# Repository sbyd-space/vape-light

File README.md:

# vape flashlight
An educational DIY kit for converting a disposable vape into a rechargeable flashlight

*early prototype of the kit photographed by Daniel Wilkens, used under CC BY 4.0 / cropped from original*

The kit is used in workshops to educate about:
* environmental and social impact of resource extraction
* resource consumption of electronics and disposable products
* basic hands-on soldering skills

It is accompanied by a [zine][zine] containing contextual information about these topics and instructions for assembly.

*rendering of the pcb by Steffen Hartwig, licensed under CC BY 4.0*

The pcbs were developed with [KiCad 8.0][kicad].  
[KiKit 1.6.0][kikit] was used for the panelization of the PCBs for production.  
Visualizations were made with [Blender 4.2][blender] and [pcb2blender 2.15][pcb2blender].  
The fabrication files were generated with [Fabrication Toolkit 5.0.1][fabricationtoolkit].  
The files for 3D printing were generated from [OpenSCAD 2021.01][openscad].  

PCB and 3D printing source files are licensed under **CERN OHL P 2.0**  
Images and visualizations are licensed under **CC BY 4.0** 

The kit, workshop and zine were developed in the project ["Sustainability by Design"][sbyd] as part of the “Innovative University” funding line and is supported by the German Federal Ministry of Research, Technology and Space (BMFTR) and the Joint Science Conference (GWK).

[zine]: https://sbyd.space/wp-content/uploads/2024/09/SBYD-Zine_3_WEB.pdf
[sbyd]: https://sbyd.space/en/

[kicad]: https://www.kicad.org
[kikit]: https://github.com/yaqwsx/KiKit
[blender]: https://www.blender.org
[pcb2blender]: https://github.com/30350n/pcb2blender
[fabricationtoolkit]: https://github.com/bennymeg/JLC-Plugin-for-KiCad
[openscad]: https://openscad.org

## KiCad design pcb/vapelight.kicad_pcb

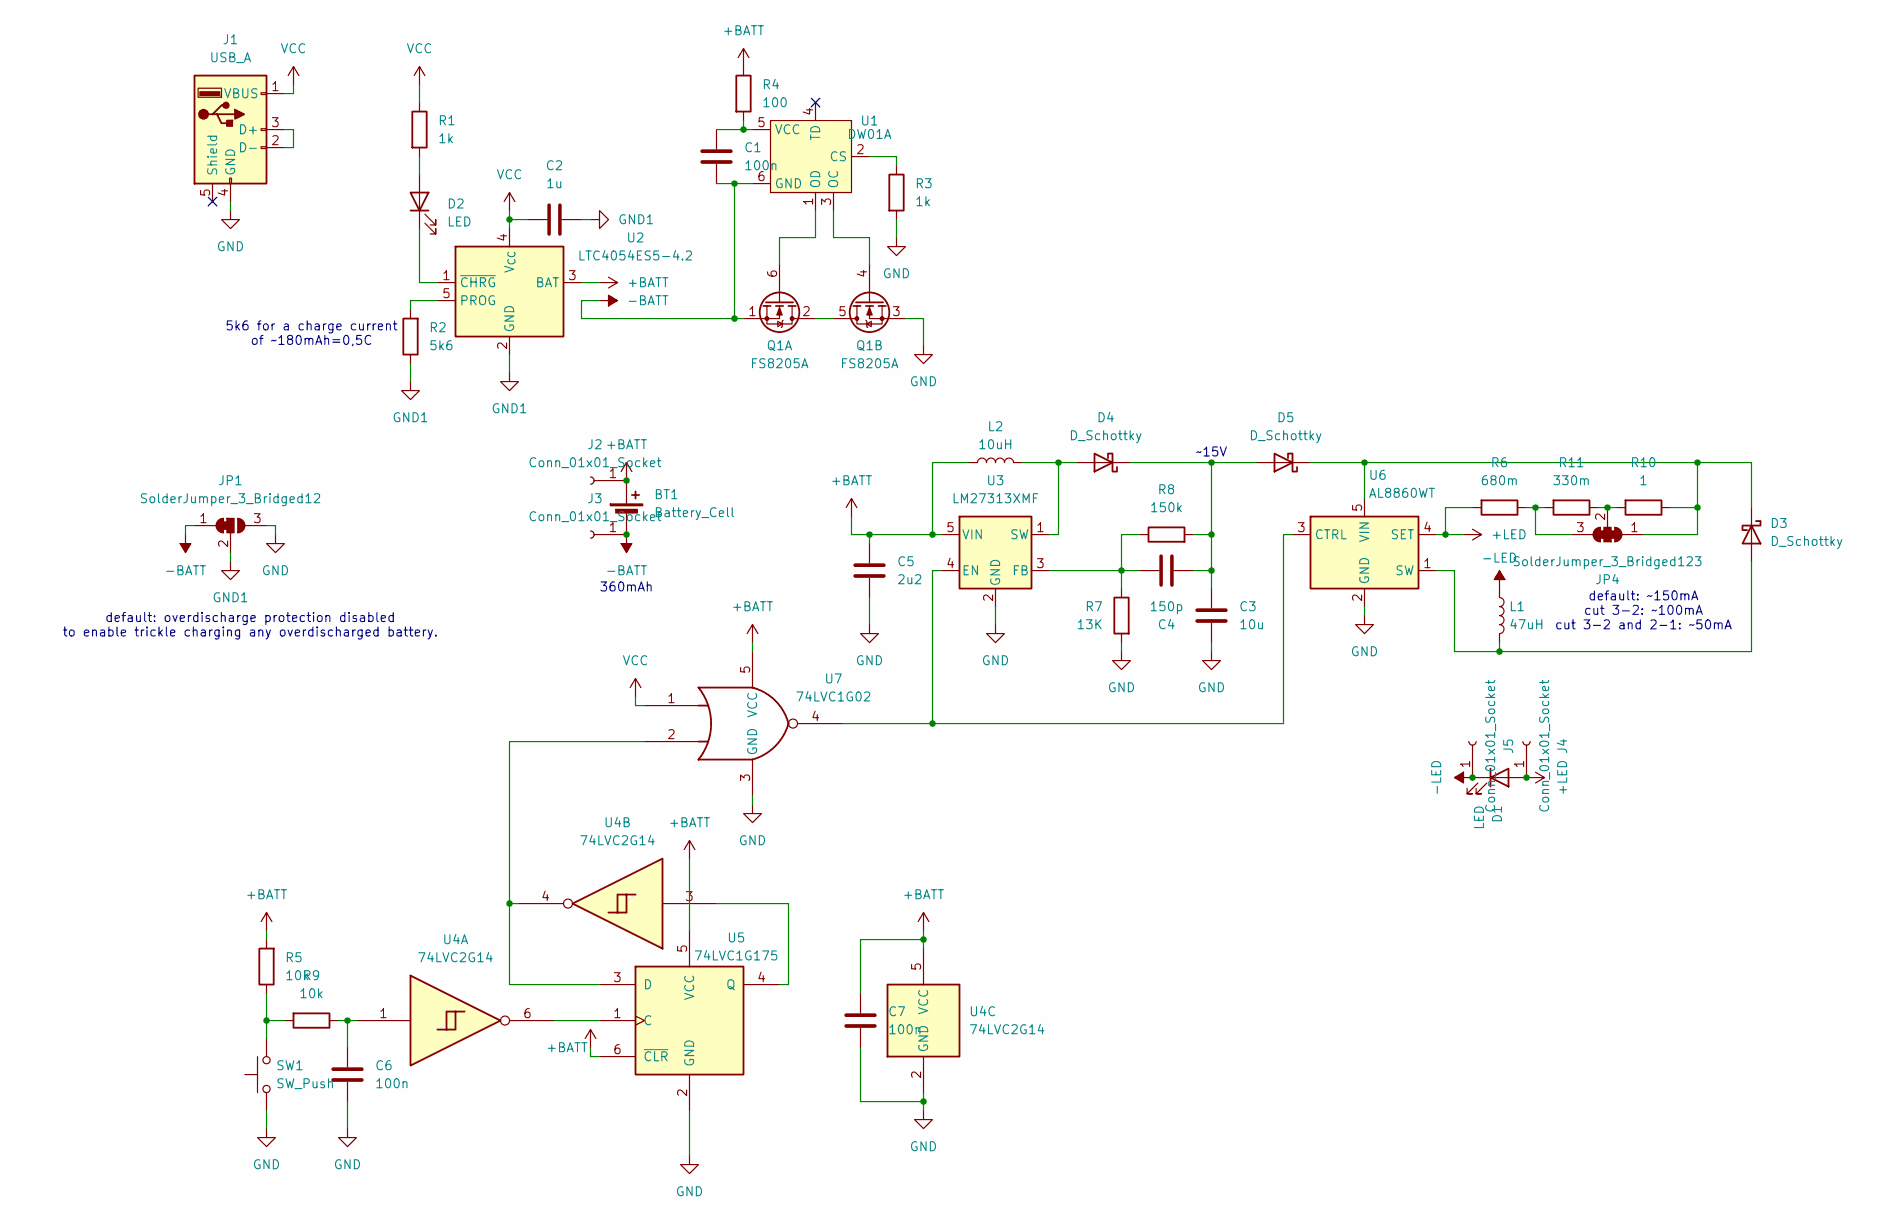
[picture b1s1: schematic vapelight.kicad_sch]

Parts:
BT1: Battery_Cell
C1, C6, C7: 100n; C_0603_1608Metric; LCSC C14663
C2: 1u; C_0603_1608Metric; LCSC C15849
C3: 10u; C_0603_1608Metric; LCSC C96446
C4: 150p; C_0603_1608Metric; LCSC C1594
C5: 2u2; C_0603_1608Metric; LCSC C23630
D1: LED
D2: LED; LED_0603_1608Metric; LCSC C2286
D3, D4, D5: D_Schottky; D_SOD-323; LCSC C191023
J1: USB_A; PCB_USB
J2, J3, J4, J5: Conn_01x01_Socket; Pin_D1.0mm_L10.0mm
JP1: SolderJumper_3_Bridged12; SolderJumper-3_P1.3mm_Bridged12_RoundedPad1.0x1.5mm
JP4: SolderJumper_3_Bridged123; SolderJumper-3_P1.3mm_Bridged123_RoundedPad1.0x1.5mm
L1: 47uH; L_3x3; LCSC C370426
L2: 10uH; L_3x3; LCSC C45403
Q1: FS8205A; SOT-23-6; LCSC C2830320
R1, R3: 1k; R_0603_1608Metric; LCSC C21190
R2: 5k6; R_0603_1608Metric; LCSC C23189
R4: 100; R_0603_1608Metric; LCSC C22775
R5, R9: 10k; R_0603_1608Metric; LCSC C25804
R6: 680m; R_0603_1608Metric; LCSC C5126049
R7: 13K; R_0603_1608Metric; LCSC C22797
R8: 150k; R_0603_1608Metric; LCSC C22807
R10: 1; R_0603_1608Metric; LCSC C22936
R11: 330m; R_0603_1608Metric; LCSC C2934252
SW1: SW_Push; SW_Push_1P1T_XKB_TS-1187A; LCSC C318886
U1: DW01A; SOT-23-6; LCSC C2927799
U2: LTC4054ES5-4.2; SOT-23-5; LCSC C478383
U3: LM27313XMF; SOT-23-5; LCSC C341750
U4: 74LVC2G14; SOT-23-6; LCSC C5375976
U5: 74LVC1G175; SOT-23-6; LCSC C128412
U6: AL8860WT; TSOT-23-5; LCSC C125330
U7: 74LVC1G02; SOT-23-5; LCSC C16360

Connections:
+BATT: BT1.1 (+), C5.1, C7.2, J2.1, L2.1, R4.1, R5.2, U2.3 (BAT), U3.5 (VIN), U4.5 (VCC), U5.5 (VCC), U5.6 (~CLR), U7.5 (VCC)
+LED: D1.2 (A), J4.1, R6.2, U6.4 (SET)
-BATT: BT1.2 (-), C1.2, J3.1, JP1.1 (A), Q1.1 (S1), U1.6 (GND)
-LED: D1.1 (K), J5.1, L1.1
GND: C3.2, C5.2, C6.1, C7.1, J1.4 (GND), JP1.3 (B), Q1.3 (S2), R3.2, R7.2, SW1.1, U3.2 (GND), U4.2 (GND), U5.2 (GND), U6.2 (GND), U7.3 (GND)
GND1: C2.2, JP1.2 (C), R2.1, U2.2 (GND)
unnamed: C6.2, R9.1, U4.1
unnamed: D2.2 (A), R1.2
unnamed: D2.1 (K), U2.1 (~CHRG)
unnamed: D3.2 (A), L1.2, U6.1 (SW)
unnamed: D3.1 (K), D5.1 (K), JP4.1 (A), R10.1, U6.5 (VIN)
unnamed: D4.2 (A), L2.2, U3.1 (SW)
unnamed: C3.1, C4.1, D4.1 (K), D5.2 (A), R8.2
unnamed: J1.2 (D-), J1.3 (D+)
unnamed: JP4.3 (B), R6.1, R11.2
unnamed: JP4.2 (C), R10.2, R11.1
unnamed: Q1.2 (D1), Q1.5 (D2)
unnamed: Q1.6 (G1), U1.1 (OD)
unnamed: Q1.4 (G2), U1.3 (OC)
unnamed: R5.1, R9.2, SW1.2
unnamed: R3.1, U1.2 (CS)
unnamed: C1.1, R4.2, U1.5 (VCC)
unnamed: R2.2, U2.5 (PROG)
unnamed: U3.4 (EN), U6.3 (CTRL), U7.4
unnamed: C4.2, R7.1, R8.1, U3.3 (FB)
unnamed: U4.6, U5.1 (C)
unnamed: U4.4, U5.3 (D), U7.2
unnamed: U4.3, U5.4 (Q)
VCC: C2.1, J1.1 (VBUS), R1.1, U2.4 (V_{CC}), U7.1

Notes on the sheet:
~15V
default: ~150mA cut 3-2: ~100mA cut 3-2 and 2-1: ~50mA
default: overdischarge protection disabled to enable trickle charging any overdischarged battery.
360mAh
5k6 for a charge current of ~180mAh=0,5C

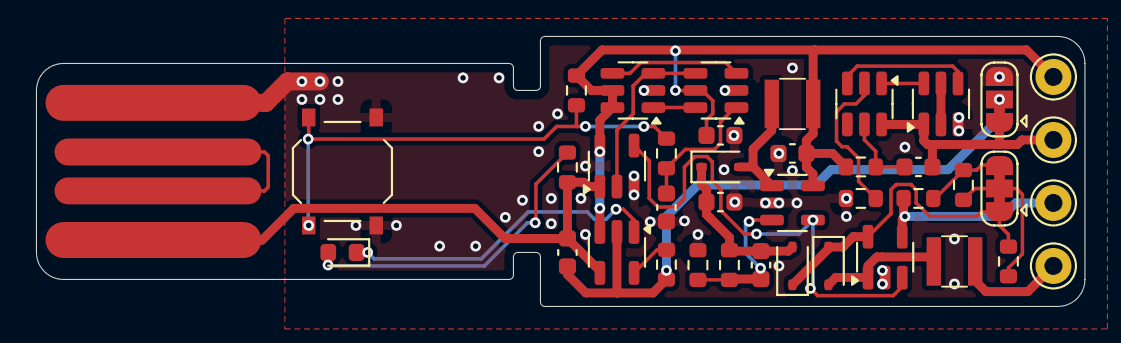
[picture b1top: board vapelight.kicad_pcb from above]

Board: 2 copper layers, 58.2 x 15.0 mm, 40 parts (0 on the bottom side), 29 nets.

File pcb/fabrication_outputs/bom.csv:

Designator,Footprint,Quantity,Value,LCSC Part #
"0-C1, 0-C6, 0-C7, 1-C1, 1-C6, 1-C7, 2-C1, 2-C6, 2-C7, 3-C1, 3-C6, 3-C7",0603,12,100n,C14663
"0-C2, 1-C2, 2-C2, 3-C2",0603,4,1u,C15849
"0-C3, 1-C3, 2-C3, 3-C3",0603,4,10u,C96446
"0-C4, 1-C4, 2-C4, 3-C4",0603,4,150p,C1594
"0-C5, 1-C5, 2-C5, 3-C5",0603,4,2u2,C23630
"0-D2, 1-D2, 2-D2, 3-D2",0603,4,LED,C2286
"0-D3, 0-D4, 0-D5, 1-D3, 1-D4, 1-D5, 2-D3, 2-D4, 2-D5, 3-D3, 3-D4, 3-D5",D_SOD-323,12,D_Schottky,C191023
"0-L1, 1-L1, 2-L1, 3-L1",L_3x3,4,47uH,C370426
"0-L2, 1-L2, 2-L2, 3-L2",L_3x3,4,10uH,C45403
"0-Q1, 1-Q1, 2-Q1, 3-Q1",SOT-23-6,4,FS8205A,C2830320
"0-R1, 1-R1, 2-R1, 3-R1",0603,4,180,C22828
"0-R10, 1-R10, 2-R10, 3-R10",0603,4,1,C22936
"0-R11, 1-R11, 2-R11, 3-R11",0603,4,330m,C2934252
"0-R2, 1-R2, 2-R2, 3-R2",0603,4,5k6,C23189
"0-R3, 1-R3, 2-R3, 3-R3",0603,4,1k,C21190
"0-R4, 1-R4, 2-R4, 3-R4",0603,4,100,C22775
"0-R5, 1-R5, 2-R5, 3-R5",0603,4,10k	,C25804
"0-R6, 1-R6, 2-R6, 3-R6",0603,4,680m,C5126049
"0-R7, 1-R7, 2-R7, 3-R7",0603,4,13K,C22797
"0-R8, 1-R8, 2-R8, 3-R8",0603,4,150k,C22807
"0-R9, 1-R9, 2-R9, 3-R9",0603,4,10k,C25804
"0-SW1, 1-SW1, 2-SW1, 3-SW1",SW_Push_1P1T_XKB_TS-1187A,4,SW_Push,C571338
"0-U1, 1-U1, 2-U1, 3-U1",SOT-23-6,4,DW01A,C2927799
"0-U2, 1-U2, 2-U2, 3-U2",SOT-23-5,4,LTC4054ES5-4.2,C478383
"0-U3, 1-U3, 2-U3, 3-U3",SOT-23-5,4,LM27313XMF,C341750
"0-U4, 1-U4, 2-U4, 3-U4",SOT-23-6,4,74LVC2G14,C5375976
"0-U5, 1-U5, 2-U5, 3-U5",SOT-23-6,4,74LVC1G175,C128412
"0-U6, 1-U6, 2-U6, 3-U6",TSOT-23-5,4,AL8860WT,C125330
"0-U7, 1-U7, 2-U7, 3-U7",SOT-23-5,4,74LVC1G02,C16360

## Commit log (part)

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2024-08-27 licensing
2024-08-27 remove licensing
2024-08-27 Create LICENCE-CERN-OHL-P.txt
    licensing: add CERN OHL
2024-08-27 Create LICENSE-CC-BY.txt
    licensing: add CC-BY
2024-08-27 .gitignore: remove .DS_Store
2024-08-27 .gitignore is now working
2024-09-03 license update
2025-04-30 Revision E
2025-04-30 fix for zine link
2025-05-08 updated and optimized images
    Switched to jpg: smaller files.
    Added photo of complete kit.
2025-05-23 Revision F
    – less bright charge LED
    – higher button
    – different sizes of panelized fabrication outputs
    - minor fixes
2025-06-11 optimized 3D printed part
2026-02-20 added alternative printed part for elfbar 800

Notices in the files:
README.md:
License: CC BY 4.0
Licence: CERN OHL P 2.0
